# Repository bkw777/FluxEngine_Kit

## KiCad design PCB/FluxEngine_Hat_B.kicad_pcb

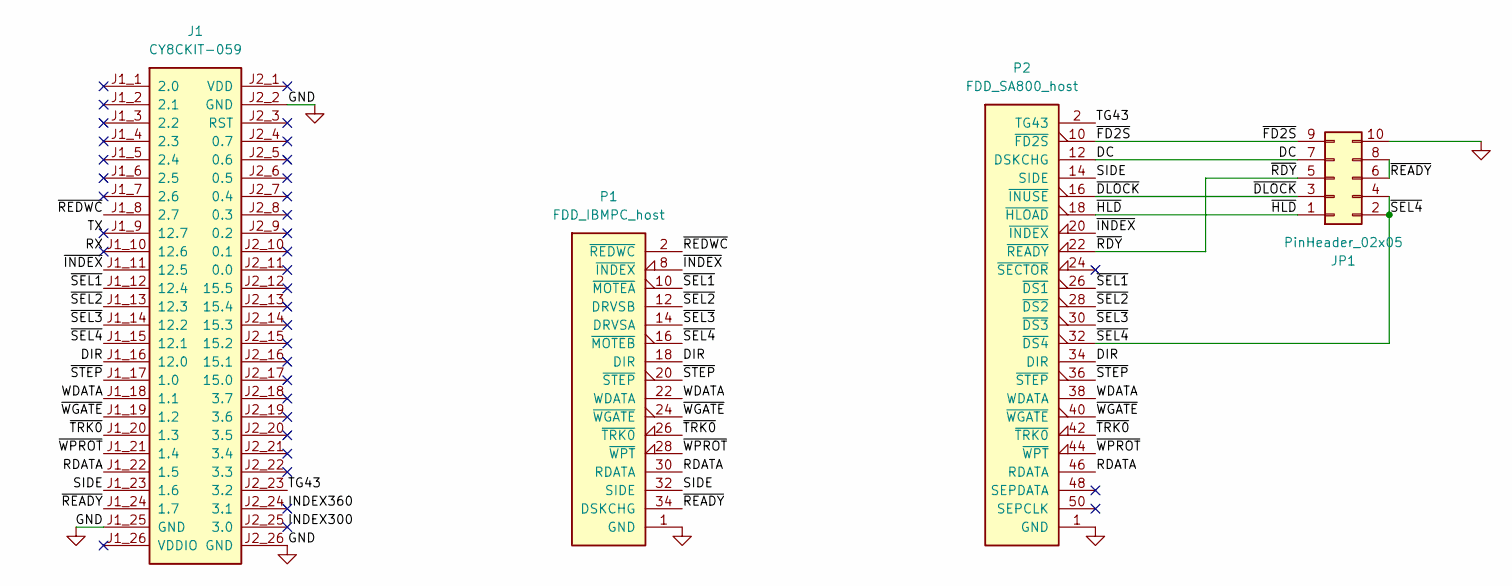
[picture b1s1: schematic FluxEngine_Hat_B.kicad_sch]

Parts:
J1: CY8CKIT-059
JP1: PinHeader_02x05; PinHeader_2x05_P2.54mm_Vertical
P1: FDD_IBMPC_host; IDC-Header_2x17_P2.54mm_Latch_Vertical - FDD
P2: FDD_SA800_host; IDC-Header_2x25_P2.54mm_Latch_Vertical

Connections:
/DC: JP1.7, P2.12 (DSKCHG)
/DIR: J1.J1_16 (12.0), P1.18 (DIR), P2.34 (DIR)
/INDEX300: J1.J2_25 (3.0)
/INDEX360: J1.J2_24 (3.1)
/RDATA: J1.J1_22 (1.5), P1.30 (RDATA), P2.46 (RDATA)
/RX: J1.J1_10 (12.6)
/SIDE: J1.J1_23 (1.6), P1.32 (SIDE), P2.14 (SIDE)
/TG43: J1.J2_23 (3.2), P2.2 (TG43)
/TX: J1.J1_9 (12.7)
/WDATA: J1.J1_18 (1.1), P1.22 (WDATA), P2.38 (WDATA)
/~DLOCK: JP1.3, P2.16 (~INUSE)
/~FD2S: JP1.9, P2.10 (~FD2S)
/~HLD: JP1.1, P2.18 (~HLOAD)
/~INDEX: J1.J1_11 (12.5), P1.8 (~INDEX), P2.20 (~INDEX)
/~RDY: JP1.5, P2.22 (~READY)
/~READY: J1.J1_24 (1.7), JP1.6, JP1.8, P1.34 (DSKCHG)
/~REDWC: J1.J1_8 (2.7), P1.2 (~REDWC)
/~SEL1: J1.J1_12 (12.4), P1.10 (~MOTEA), P2.26 (~DS1)
/~SEL2: J1.J1_13 (12.3), P1.12 (DRVSB), P2.28 (~DS2)
/~SEL3: J1.J1_14 (12.2), P1.14 (DRVSA), P2.30 (~DS3)
/~SEL4: J1.J1_15 (12.1), JP1.2, JP1.4, P1.16 (~MOTEB), P2.32 (~DS4)
/~STEP: J1.J1_17 (1.0), P1.20 (~STEP), P2.36 (~STEP)
/~TRK0: J1.J1_20 (1.3), P1.26 (~TRK0), P2.42 (~TRK0)
/~WGATE: J1.J1_19 (1.2), P1.24 (~WGATE), P2.40 (~WGATE)
/~WPROT: J1.J1_21 (1.4), P1.28 (~WPT), P2.44 (~WPT)
GND: J1.J1_25 (GND), J1.J2_2 (GND), J1.J2_26 (GND), JP1.10, P1.1 (GND), P1.7 (GND), P1.9 (GND), P1.11 (GND), P1.13 (GND), P1.15 (GND), P1.17 (GND), P1.19 (GND), P1.21 (GND), P1.23 (GND), P1.25 (GND), P1.27 (GND), P1.29 (GND), P1.31 (GND), P1.33 (GND), P2.1 (GND), P2.3 (GND), P2.5 (GND), P2.7 (GND), P2.9 (GND), P2.11 (GND), P2.13 (GND), P2.15 (GND), P2.17 (GND), P2.19 (GND), P2.21 (GND), P2.23 (GND), P2.25 (GND), P2.27 (GND), P2.29 (GND), P2.31 (GND), P2.33 (GND), P2.35 (GND), P2.37 (GND), P2.39 (GND), P2.41 (GND), P2.43 (GND), P2.45 (GND), P2.47 (GND), P2.49 (GND)

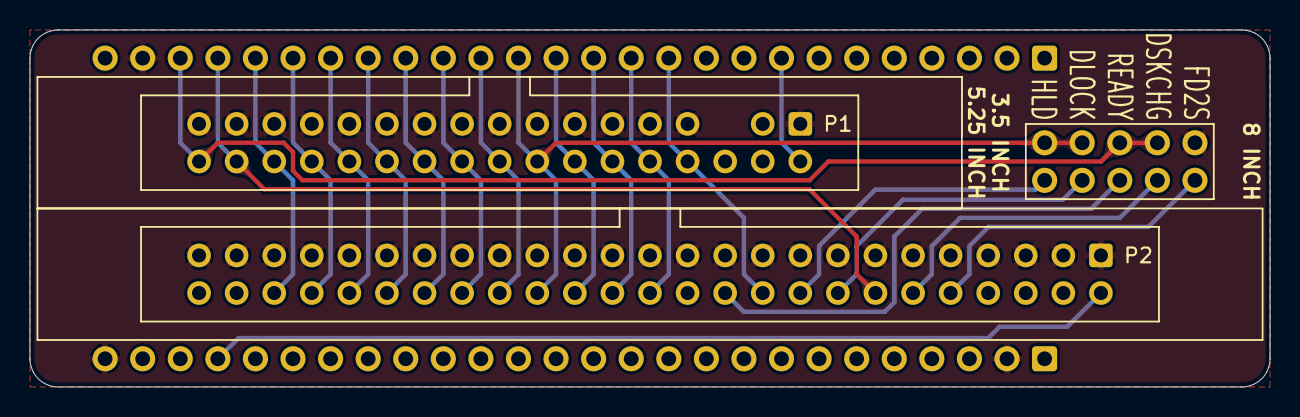
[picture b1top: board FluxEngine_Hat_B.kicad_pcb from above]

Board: 2 copper layers, 83.8 x 24.1 mm, 4 parts (0 on the bottom side), 22 nets.

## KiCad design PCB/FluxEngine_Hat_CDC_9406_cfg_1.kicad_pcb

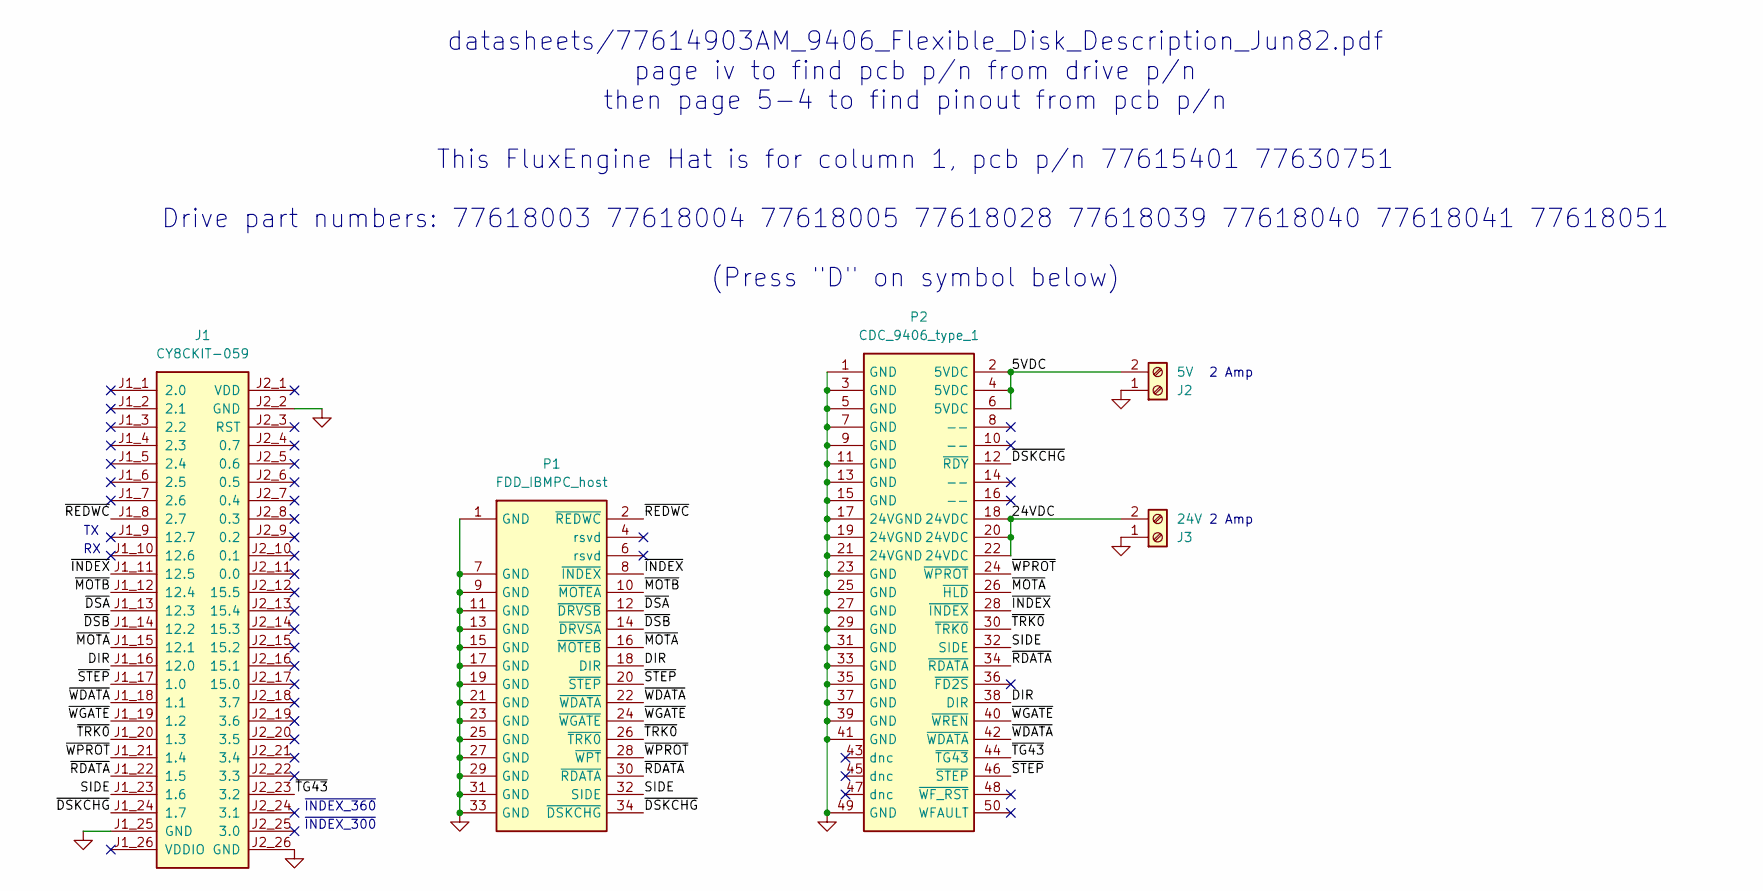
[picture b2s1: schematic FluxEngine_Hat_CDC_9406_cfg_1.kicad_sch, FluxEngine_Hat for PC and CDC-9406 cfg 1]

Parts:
J1: CY8CKIT-059; CY8CKIT-059 dry fit
J2: 5V; ScrewTerminal_1x02_P3.5mm_vertical
J3: 24V; ScrewTerminal_1x02_P3.5mm_vertical
P1: FDD_IBMPC_host; IDC-Header_2x17_P2.54mm_Latch_Vertical - FDD
P2: CDC_9406_type_1; IDC-Header_2x25_P2.54mm_Latch_Vertical

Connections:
/5VDC: J2.2, P2.2 (5VDC), P2.4 (5VDC), P2.6 (5VDC)
/24VDC: J3.2, P2.18 (24VDC), P2.20 (24VDC), P2.22 (24VDC)
/DIR: J1.J1_16 (12.0), P1.18 (DIR), P2.38 (DIR)
/SIDE: J1.J1_23 (1.6), P1.32 (SIDE), P2.32 (SIDE)
/~DSA: J1.J1_13 (12.3), P1.12 (~DRVSB)
/~DSB: J1.J1_14 (12.2), P1.14 (~DRVSA)
/~DSKCHG: J1.J1_24 (1.7), P1.34 (~DSKCHG), P2.12 (~RDY)
/~INDEX: J1.J1_11 (12.5), P1.8 (~INDEX), P2.28 (~INDEX)
/~MOTA: J1.J1_15 (12.1), P1.16 (~MOTEB), P2.26 (~HLD)
/~MOTB: J1.J1_12 (12.4), P1.10 (~MOTEA)
/~RDATA: J1.J1_22 (1.5), P1.30 (~RDATA), P2.34 (~RDATA)
/~REDWC: J1.J1_8 (2.7), P1.2 (~REDWC)
/~STEP: J1.J1_17 (1.0), P1.20 (~STEP), P2.46 (~STEP)
/~TG43: J1.J2_23 (3.2), P2.44 (~TG43)
/~TRK0: J1.J1_20 (1.3), P1.26 (~TRK0), P2.30 (~TRK0)
/~WDATA: J1.J1_18 (1.1), P1.22 (~WDATA), P2.42 (~WDATA)
/~WGATE: J1.J1_19 (1.2), P1.24 (~WGATE), P2.40 (~WREN)
/~WPROT: J1.J1_21 (1.4), P1.28 (~WPT), P2.24 (~WPROT)
GND: J1.J1_25 (GND), J1.J2_2 (GND), J1.J2_26 (GND), J2.1, J3.1, P1.1 (GND), P1.7 (GND), P1.9 (GND), P1.11 (GND), P1.13 (GND), P1.15 (GND), P1.17 (GND), P1.19 (GND), P1.21 (GND), P1.23 (GND), P1.25 (GND), P1.27 (GND), P1.29 (GND), P1.31 (GND), P1.33 (GND), P2.1 (GND), P2.3 (GND), P2.5 (GND), P2.7 (GND), P2.9 (GND), P2.11 (GND), P2.13 (GND), P2.15 (GND), P2.17 (24VGND), P2.19 (24VGND), P2.21 (24VGND), P2.23 (GND), P2.25 (GND), P2.27 (GND), P2.29 (GND), P2.31 (GND), P2.33 (GND), P2.35 (GND), P2.37 (GND), P2.39 (GND), P2.41 (GND), P2.49 (GND)

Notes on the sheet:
~{INDEX_300}
datasheets/77614903AM_9406_Flexible_Disk_Description_Jun82.pdf page iv to find pcb p/n from drive p/n then page 5-4 to find pinout from pcb p/n This FluxEngine Hat is for column 1, pcb p/n 77615401 77630751 Drive part numbers: 77618003 77618004 77618005 77618028 77618039 77618040 77618041 77618051 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
2 Amp
~{INDEX_360}

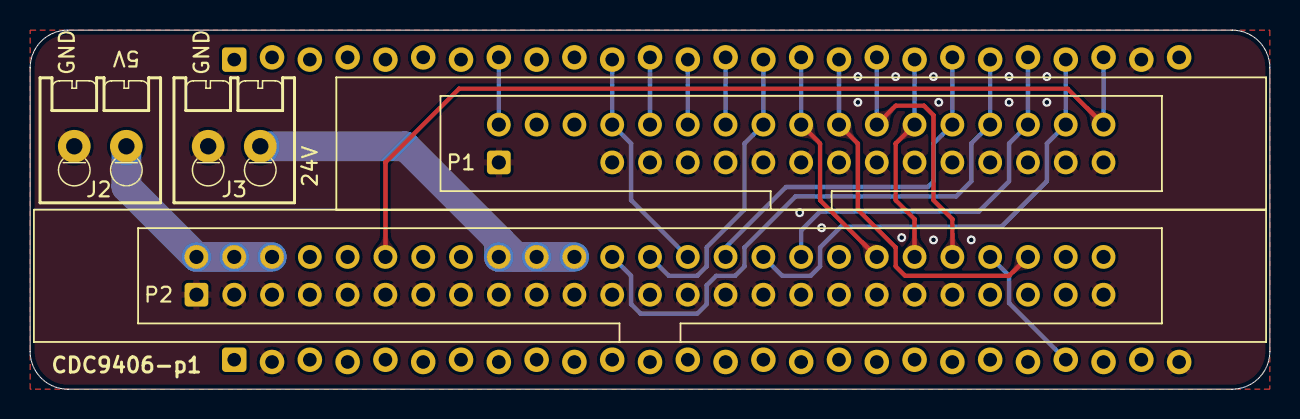
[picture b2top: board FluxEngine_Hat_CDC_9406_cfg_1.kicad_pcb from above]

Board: 2 copper layers, 83.3 x 24.1 mm, 5 parts (1 on the bottom side), 19 nets.

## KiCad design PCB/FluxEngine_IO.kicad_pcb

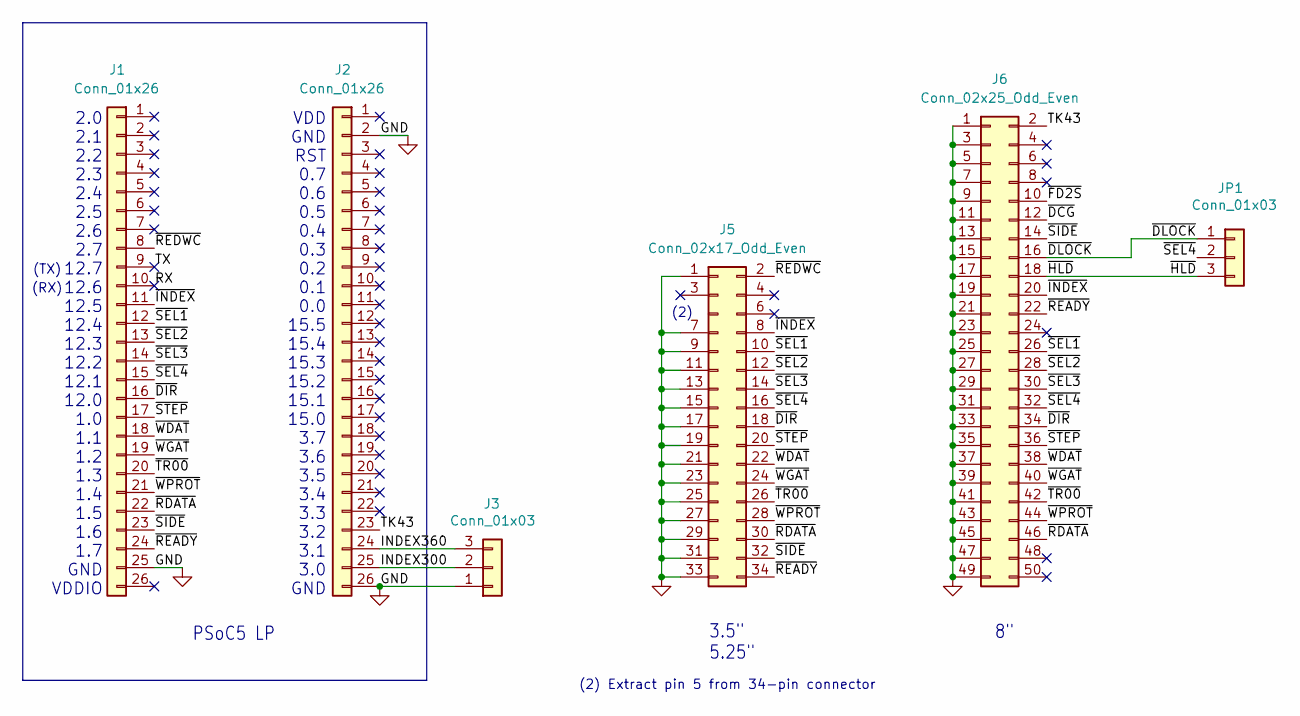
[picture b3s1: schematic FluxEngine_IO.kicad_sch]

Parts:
J1, J2: Conn_01x26; PinHeader_1x26_P2.54mm_Vertical
J3: Conn_01x03; PinHeader_1x03_P2.54mm_Vertical
J5: Conn_02x17_Odd_Even; IDC-Header_2x17_P2.54mm_Latch_Vertical - FDD
J6: Conn_02x25_Odd_Even; IDC-Header_2x25_P2.54mm_Latch_Vertical
JP1: Conn_01x03; PinHeader_1x03_P2.54mm_Vertical

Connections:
/INDEX300: J2.25, J3.2
/INDEX360: J2.24, J3.3
/RX: J1.10
/TK43: J2.23, J6.2
/TX: J1.9
/~DCG: J6.12
/~DIR: J1.16, J5.18, J6.34
/~DLOCK: J6.16, JP1.1
/~FD2S: J6.10
/~HLD: J6.18, JP1.3
/~INDEX: J1.11, J5.8, J6.20
/~RDATA: J1.22, J5.30, J6.46
/~READY: J1.24, J5.34, J6.22
/~REDWC: J1.8, J5.2
/~SEL1: J1.12, J5.10, J6.26
/~SEL2: J1.13, J5.12, J6.28
/~SEL3: J1.14, J5.14, J6.30
/~SEL4: J1.15, J5.16, J6.32, JP1.2
/~SIDE: J1.23, J5.32, J6.14
/~STEP: J1.17, J5.20, J6.36
/~TR00: J1.20, J5.26, J6.42
/~WDAT: J1.18, J5.22, J6.38
/~WGAT: J1.19, J5.24, J6.40
/~WPROT: J1.21, J5.28, J6.44
GND: J1.25, J2.2, J2.26, J3.1, J5.1, J5.7, J5.9, J5.11, J5.13, J5.15, J5.17, J5.19, J5.21, J5.23, J5.25, J5.27, J5.29, J5.31, J5.33, J6.1, J6.3, J6.5, J6.7, J6.9, J6.11, J6.13, J6.15, J6.17, J6.19, J6.21, J6.23, J6.25, J6.27, J6.29, J6.31, J6.33, J6.35, J6.37, J6.39, J6.41, J6.43, J6.45, J6.47, J6.49

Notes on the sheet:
3.5" 5.25"
(2)
(2) Extract pin 5 from 34-pin connector
(RX)
PSoC5 LP
2.0 2.1 2.2 2.3 2.4 2.5 2.6 2.7 12.7 12.6 12.5 12.4 12.3 12.2 12.1 12.0 1.0 1.1 1.2 1.3 1.4 1.5 1.6 1.7 GND VDDIO
VDD GND RST 0.7 0.6 0.5 0.4 0.3 0.2 0.1 0.0 15.5 15.4 15.3 15.2 15.1 15.0 3.7 3.6 3.5 3.4 3.3 3.2 3.1 3.0 GND
(TX)

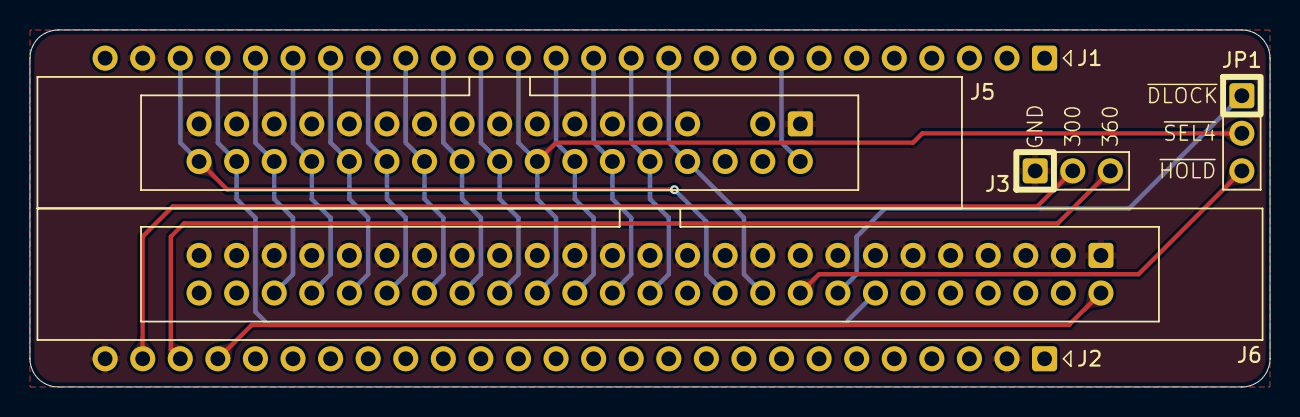
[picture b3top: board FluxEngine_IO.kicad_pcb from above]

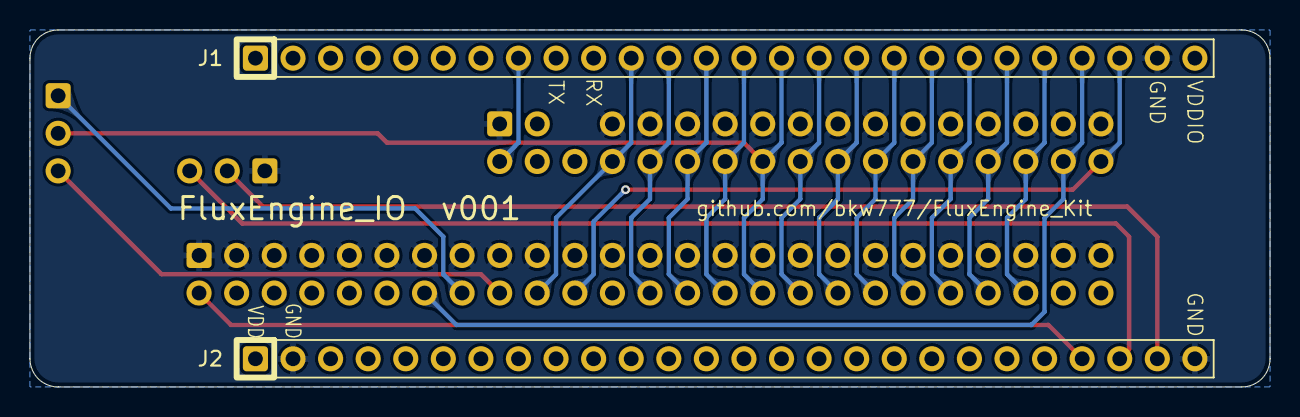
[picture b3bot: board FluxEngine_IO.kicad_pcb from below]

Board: 2 copper layers, 83.8 x 24.1 mm, 6 parts (2 on the bottom side), 21 nets.

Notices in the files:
PCB/FluxEngine_Hat_B.kicad_sch:
CC BY-SA
